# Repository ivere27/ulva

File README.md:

# Ulva

An open-source ESP32-C5 controller board for robotics and controlled-environment agriculture (CEA).

The repository contains a 100 × 100 mm, two-layer carrier PCB, eight KiCad
schematic sheets, project libraries and an ESP-IDF button-input example.
The current board revision is **v0.42**.

- Two CAN FD interfaces with fused 24 V control-power outputs.
- 24 V DC input and an onboard 5 V supply.
- Two I²C buses, peripheral connections and
  [OpenSprinkler-compatible AC/DC expansion](docs/hardware.md#opensprinkler-acdc-expansion).
- OLED, RTC, DHT20, 433 MHz receiver and passive piezo connections.
- Three ADC buttons, a two-switch configuration input and voltage monitoring.

This is a prototype. Full controller firmware and physical validation remain
unfinished. See the [hardware reference](docs/hardware.md) for pin assignments,
power limits and wiring.

## Board views

CAD renders of the current board:

| Front | Back |
| --- | --- |
|  |  |
| **Routing** | **3D assembly** |
|  |  |

[Interactive board viewer](https://ivere27.github.io/ulva/)
· [HTML source](docs/index.html)

Switch between the Routing, 3D, Schematic and Orders tabs. Routing lets you select
traces, vias or pads to highlight a net, search components, switch copper layers,
zoom and save a selection image. Ground pours are omitted; both layers use
front-view coordinates. Schematic provides a thumbnail sidebar for all eight
sheets, with zoom, pan and a PDF download. Orders lets you select JLCPCB assembly
or loose LCSC parts and download supplier files; see the
[order workflow](tools/README.md).

For offline use, keep the complete `docs/` directory and open `docs/index.html`
directly in a browser. In Routing, choose `routing/board.svg` when prompted. In
3D, choose `3d/assembly.json` and `3d/board.glb` together. A local server is optional;
the browser needs explicit file selection to read these data files from disk.
Schematic images, the PDF and Orders open directly without a file picker.

**Version details** shows the board revision, an **Export base** commit and
source/export SHA-256 hashes. Export base records Git HEAD when the metadata was
generated. Each view retains its own recorded source hashes, so older exports
can be distinguished from the current sources.

### 3D assembly

[Open the 3D tab](https://ivere27.github.io/ulva/#3d)
· [Export and usage guide](docs/3d.md)

Rotate, zoom and pan the assembly, or show and hide individual components and
modules. Visibility controls affect the view only. Some component shapes and
module mounting heights are illustrative; the KiCad board remains authoritative.

## Open the project

Open [`ulva_controller.kicad_pro`](ulva_controller.kicad_pro) in KiCad 9 with
its standard symbol and footprint libraries installed. The included project
libraries use relative paths.

| Path | Contents |
| --- | --- |
| `ulva_*.kicad_*` | Schematics, PCB, project settings and design rules |
| `Ulva.kicad_sym`, `Ulva.pretty/` | Project symbols and footprints |
| `Ulva.3dshapes/` | Original terminal-block visualization models |
| [docs/hardware.md](docs/hardware.md) | Hardware and pinout reference |
| [docs/bom.md](docs/bom.md) | Parts and assembly ownership |
| [docs/3d.md](docs/3d.md) | 3D viewer, export and model limitations |
| [tools/](tools/README.md) | JLCPCB and LCSC order preparation and unit tests |
| [scripts/](#verification) | KiCad DRC/ERC validation, SPICE simulation and export runner |
| [firmware/buttons_adc/](firmware/buttons_adc/README.md) | Button example, host unit tests, build and integration instructions |
| `artwork/ulva-icon.svg` | Board icon |

## Verification

Use Python 3.10 or later. Button tests need CMake and a C compiler. CAD checks
use KiCad 9's `kicad-cli` and `pcbnew` module in the same Python environment,
plus `ngspice` for analog checks. Without native KiCad, the runner uses Docker
with the pinned `kicad/kicad:9.0.9` image.

From the repository root, install the rendering dependencies needed for PCB,
Gerber and board-documentation checks, then run the relevant checks:

```sh
python3 -m pip install --target build/preview-python \
  gerbonara==1.5.0 resvg-py==0.2.6
python3 -m unittest discover -s tools
python3 scripts/run_checks.py buttons
python3 scripts/run_checks.py schematic
python3 scripts/run_checks.py pcb
```

The runner checks a disposable snapshot and writes logs and receipts under
ignored `build/runs/`. Use the runner rather than invoking its export helpers
directly. Automated checks do not replace physical hardware validation.

When board images or the routing viewer need regeneration:

```sh
python3 scripts/run_checks.py board-docs
# After reviewing the generated assets, update the images and routing viewer:
python3 scripts/run_checks.py board-docs --update-docs
```

To regenerate the schematic pages and PDF, use Python 3.10 or later and KiCad 9's
`kicad-cli`. Review the output in `build/schematic-docs/`, then publish it:

```sh
python3 scripts/export_schematic_docs.py
python3 scripts/export_schematic_docs.py --update-docs
```

After updating public viewer assets, refresh their version metadata. This reads
the existing files; regenerate any affected view first:

```sh
python3 scripts/export_viewer_info.py
```

## License

Original Ulva design files, firmware, documentation and artwork are released
under the [MIT License](LICENSE). Upstream library data and dependencies retain
their own licenses; see [third-party notices](NOTICE.md).

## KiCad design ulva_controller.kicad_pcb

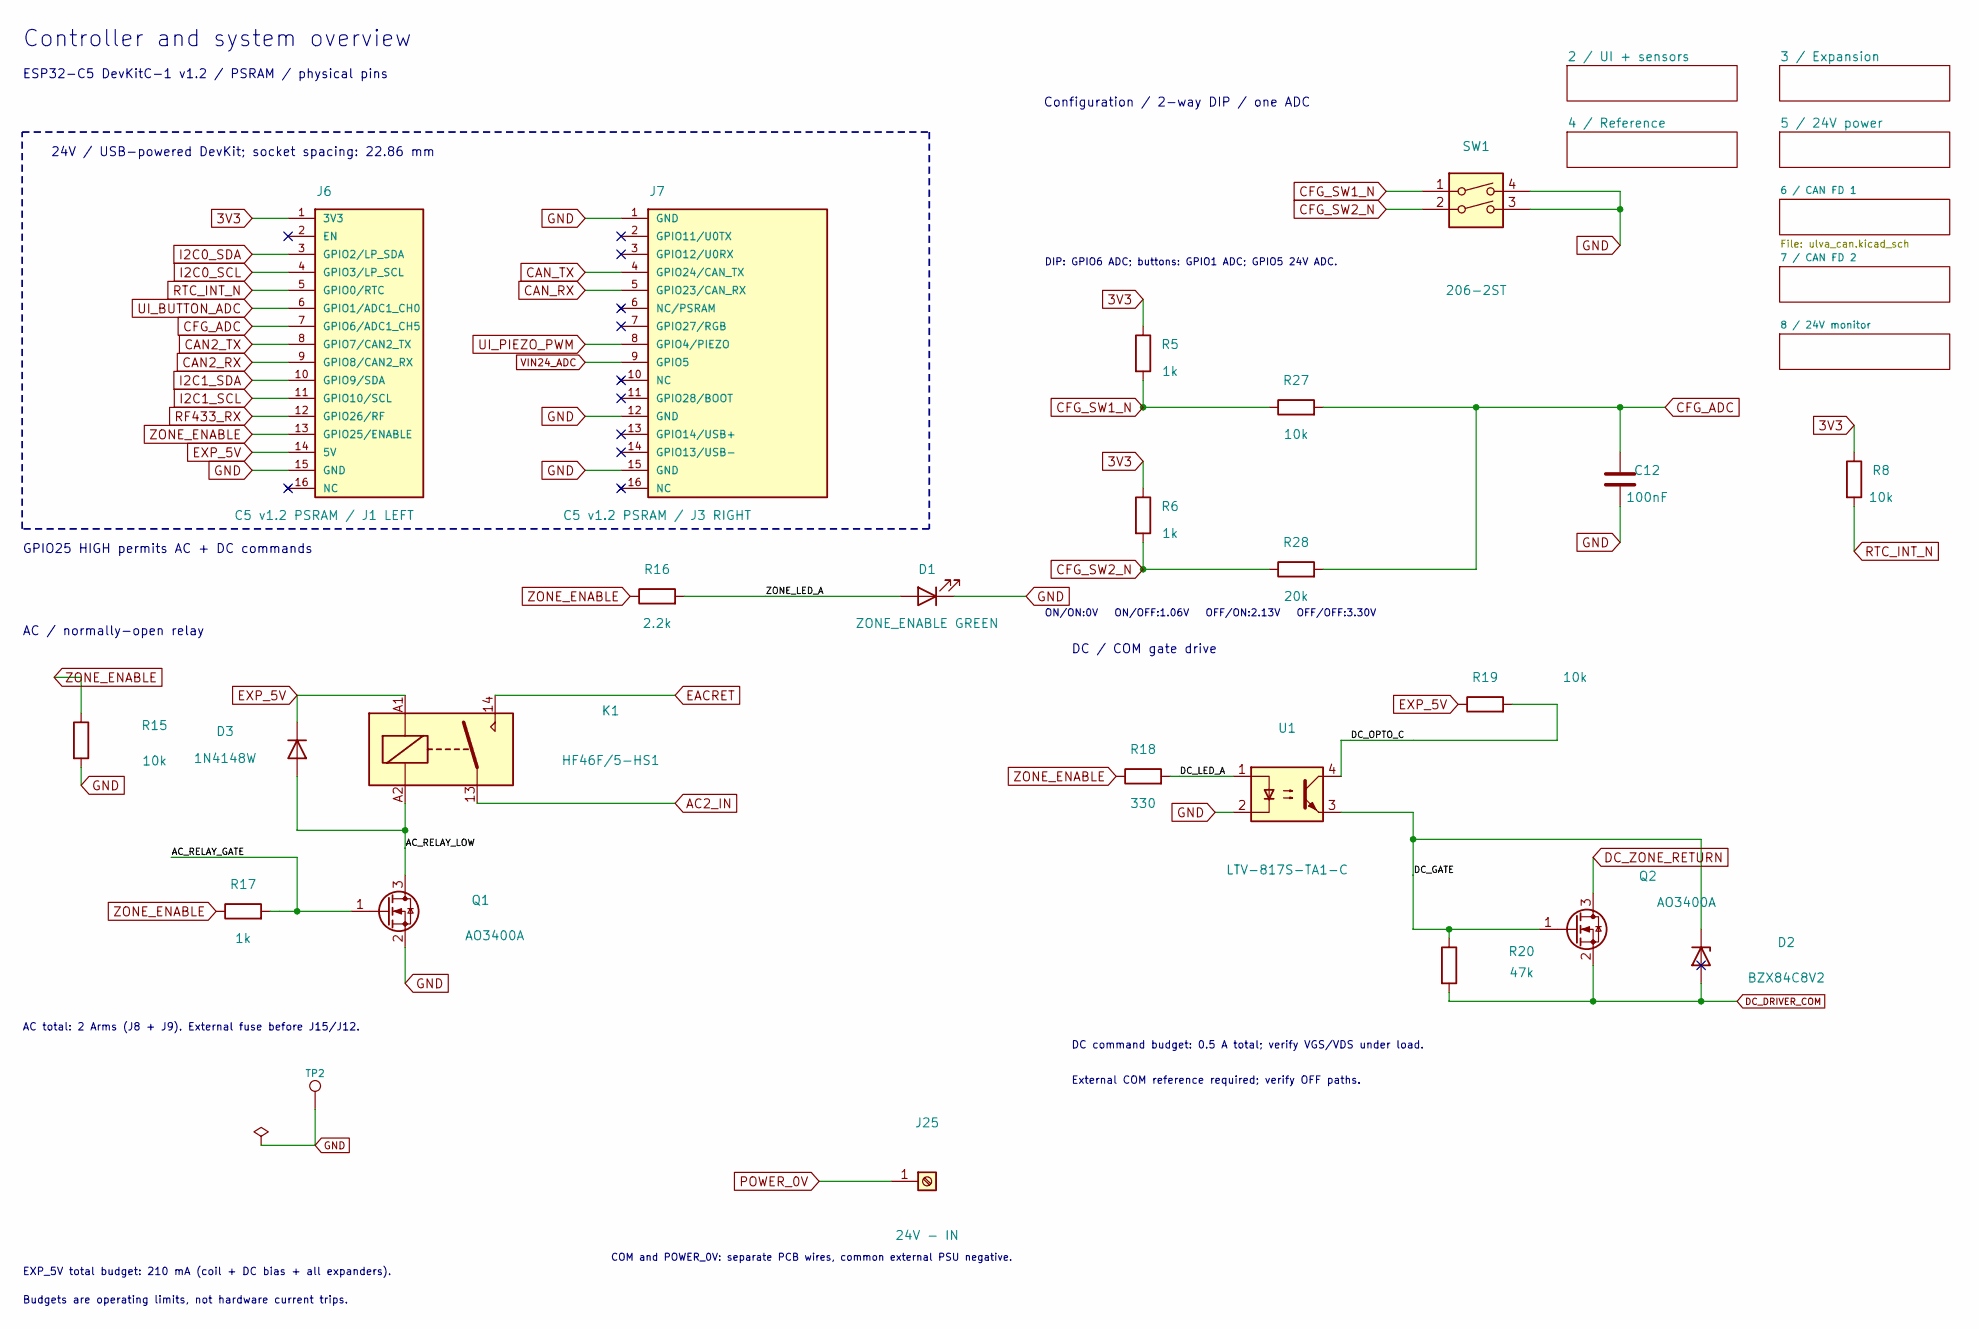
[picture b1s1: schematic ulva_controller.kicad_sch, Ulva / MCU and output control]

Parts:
C12: 100nF; C_0603_1608Metric; MPN CC0603KRX7R9BB104; LCSC C14663
D1: ZONE_ENABLE GREEN; LED_0805_2012Metric; MPN KT-0805G; LCSC C2297
D2: BZX84C8V2; SOT-23; MPN BZX84C8V2; LCSC C22395522
D3: 1N4148W; D_SOD-123; MPN 1N4148W; LCSC C81598
J6: C5 v1.2 PSRAM / J1 LEFT; Samtec_SSW-116-01-G-S_1x16_P2.54mm; MPN SSW-116-01-G-S
J7: C5 v1.2 PSRAM / J3 RIGHT; Samtec_SSW-116-01-G-S_1x16_P2.54mm; MPN SSW-116-01-G-S
J25: 24V - IN; TerminalBlock_MetzConnect_360272_1x01_Horizontal_ScrewM2.6; MPN 360272
K1: HF46F/5-HS1; Relay_SPST_Hongfa_HF46F_HS1; MPN HF46F/5-HS1
Q1, Q2: AO3400A; SOT-23; MPN AO3400A; LCSC C20917
R5, R6, R17: 1k; R_0603_1608Metric; MPN 0603WAF1001T5E; LCSC C21190
R8, R15, R19, R27: 10k; R_0603_1608Metric; MPN 0603WAF1002T5E; LCSC C25804
R16: 2.2k; R_0603_1608Metric; MPN 0603WAF2201T5E; LCSC C4190
R18: 330; R_0603_1608Metric; MPN 0603WAF3300T5E; LCSC C23138
R20: 47k; R_0603_1608Metric; MPN 0603WAF4702T5E; LCSC C25819
R28: 20k; R_0603_1608Metric; MPN 0603WAF2002T5E; LCSC C4184
SW1: 206-2ST; SW_DIP_SPSTx02_Slide_9.78x7.26mm_W7.62mm_P2.54mm; MPN 206-2ST
TP2: GND; TestPoint_Pad_D1.5mm
U1: LTV-817S-TA1-C; SMDIP-4_W9.53mm; MPN LTV-817S-TA1-C; LCSC C109227

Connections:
3V3: J6.1 (3V3), R5.1, R6.1, R8.1; also elsewhere on the board
/AC_RELAY_GATE: Q1.1 (G), R17.2
/AC_RELAY_LOW: D3.2 (A), K1.A2, Q1.3 (D)
/DC_GATE: D2.3 (K), Q2.1 (G), R20.1, U1.3
/DC_LED_A: R18.2, U1.1
/DC_OPTO_C: R19.2, U1.4
/ZONE_LED_A: D1.2 (A), R16.2
AC2_IN: K1.13; also elsewhere on the board
CAN2_RX: J6.9 (GPIO8/CAN2_RX); also elsewhere on the board
CAN2_TX: J6.8 (GPIO7/CAN2_TX); also elsewhere on the board
CAN_RX: J7.5 (GPIO23/CAN_RX); also elsewhere on the board
CAN_TX: J7.4 (GPIO24/CAN_TX); also elsewhere on the board
CFG_ADC: C12.1, J6.7 (GPIO6/ADC1_CH5), R27.2, R28.2
CFG_SW1_N: R5.2, R27.1, SW1.1
CFG_SW2_N: R6.2, R28.1, SW1.2
DC_DRIVER_COM: D2.1 (A), Q2.2 (S), R20.2; also elsewhere on the board
DC_ZONE_RETURN: Q2.3 (D); also elsewhere on the board
EACRET: K1.14; also elsewhere on the board
EXP_5V: D3.1 (K), J6.14 (5V), K1.A1, R19.1; also elsewhere on the board
GND: C12.2, D1.1 (K), J6.15 (GND), J7.1 (GND), J7.12 (GND), J7.15 (GND), Q1.2 (S), R15.2, SW1.3, SW1.4, TP2.1, U1.2; also elsewhere on the board
I2C0_SCL: J6.4 (GPIO3/LP_SCL); also elsewhere on the board
I2C0_SDA: J6.3 (GPIO2/LP_SDA); also elsewhere on the board
I2C1_SCL: J6.11 (GPIO10/SCL); also elsewhere on the board
I2C1_SDA: J6.10 (GPIO9/SDA); also elsewhere on the board
POWER_0V: J25.1; also elsewhere on the board
RF433_RX: J6.12 (GPIO26/RF); also elsewhere on the board
RTC_INT_N: J6.5 (GPIO0/RTC), R8.2; also elsewhere on the board
UI_BUTTON_ADC: J6.6 (GPIO1/ADC1_CH0); also elsewhere on the board
UI_PIEZO_PWM: J7.8 (GPIO4/PIEZO); also elsewhere on the board
VIN24_ADC: J7.9 (GPIO5); also elsewhere on the board
ZONE_ENABLE: J6.13 (GPIO25/ENABLE), R15.1, R16.1, R17.1, R18.1

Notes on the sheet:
Controller and system overview
ESP32-C5 DevKitC-1 v1.2 / PSRAM / physical pins
Configuration / 2-way DIP / one ADC
GPIO25 HIGH permits AC + DC commands
24V / USB-powered DevKit; socket spacing: 22.86 mm
AC / normally-open relay
DC / COM gate drive
AC total: 2 Arms (J8 + J9). External fuse before J15/J12.
DC command budget: 0.5 A total; verify VGS/VDS under load.
EXP_5V total budget: 210 mA (coil + DC bias + all expanders).
Budgets are operating limits, not hardware current trips.
External COM reference required; verify OFF paths.
COM and POWER_0V: separate PCB wires, common external PSU negative.
DIP: GPIO6 ADC; buttons: GPIO1 ADC; GPIO5 24V ADC.
ON/ON:0V ON/OFF:1.06V OFF/ON:2.13V OFF/OFF:3.30V

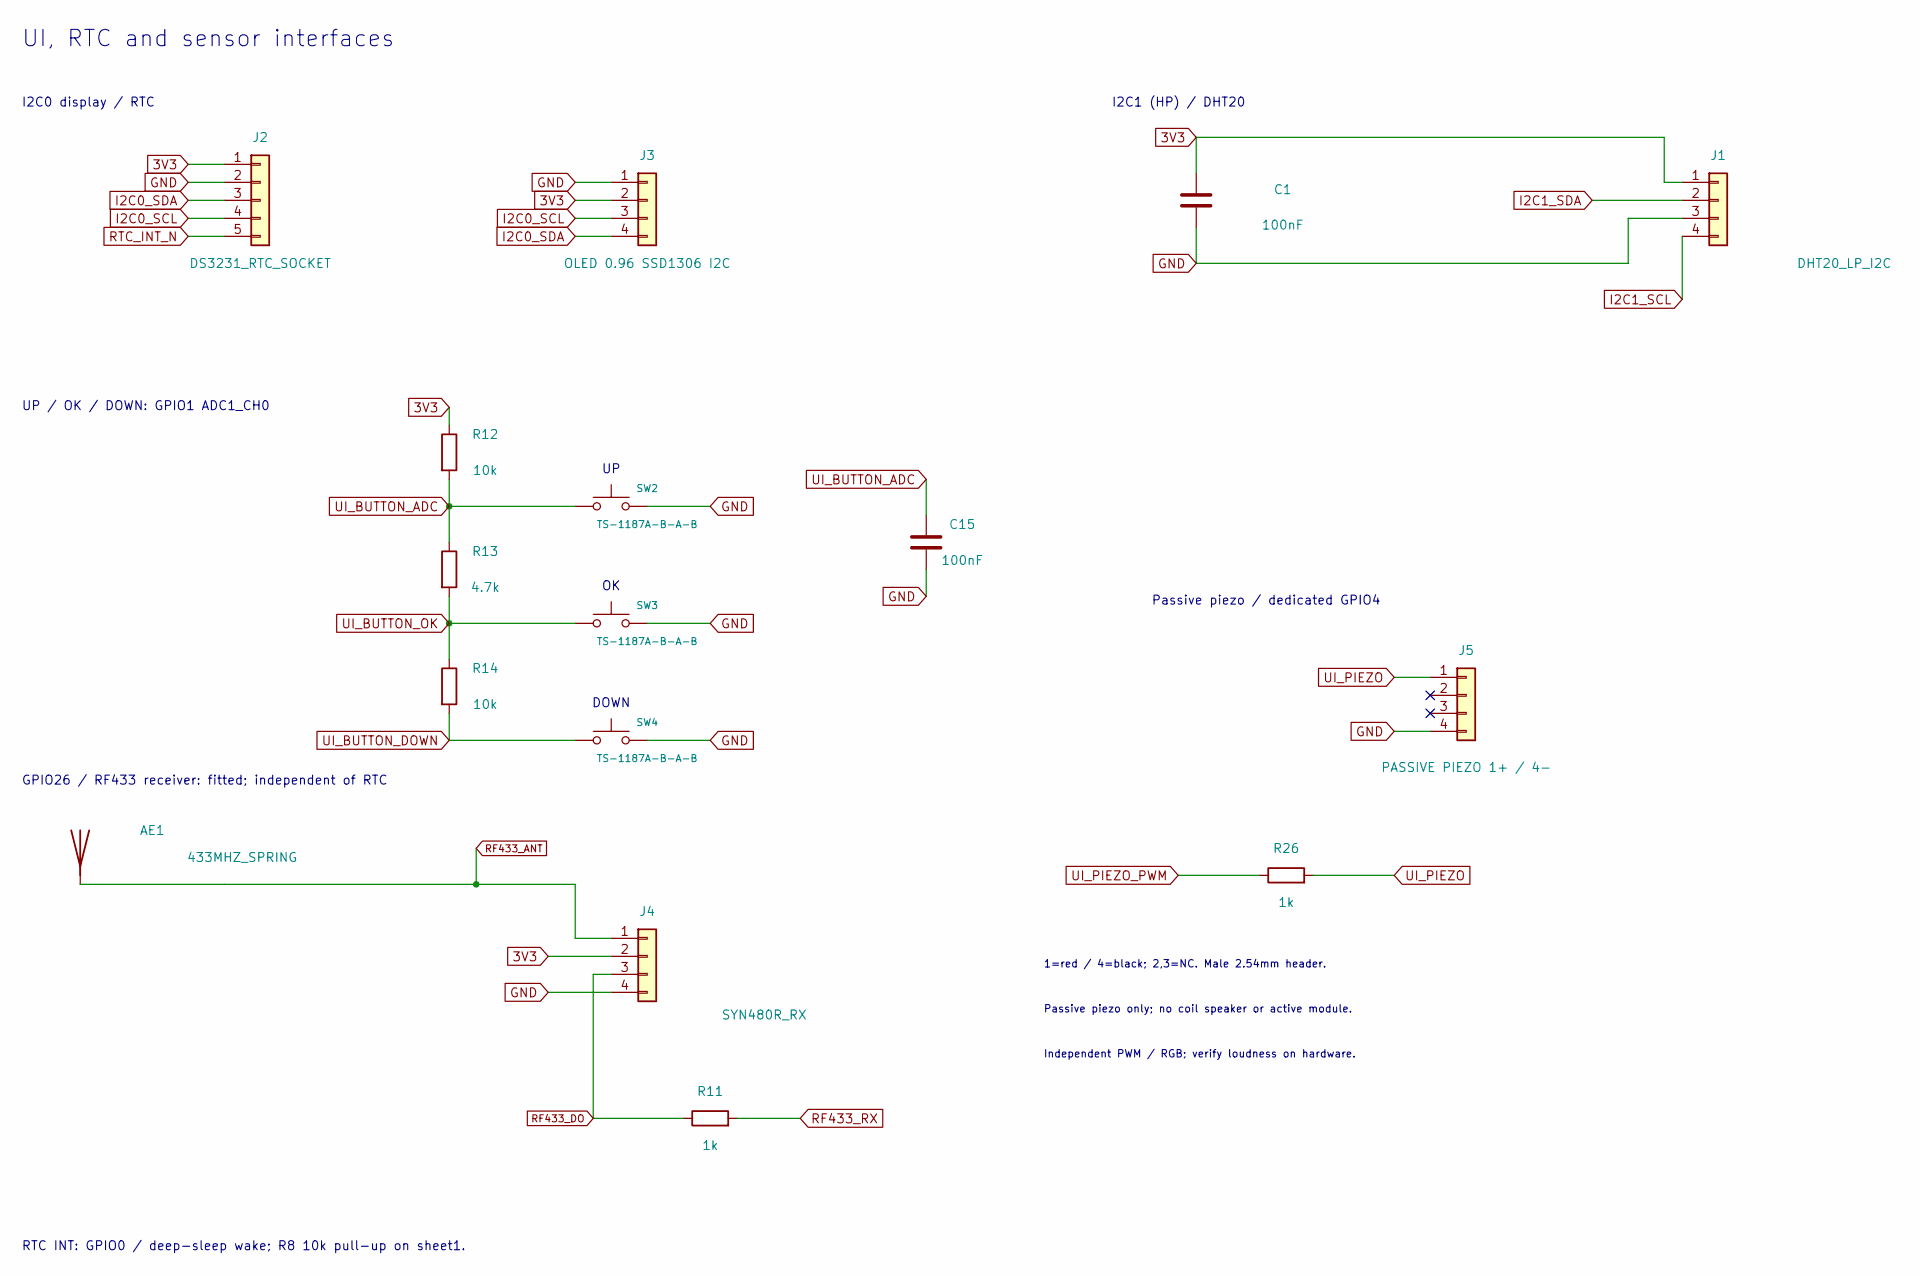
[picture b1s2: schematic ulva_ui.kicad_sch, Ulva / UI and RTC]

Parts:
AE1: 433MHZ_SPRING; TestPoint_THTPad_D2.0mm_Drill1.0mm
C1, C15: 100nF; C_0603_1608Metric; MPN CC0603KRX7R9BB104; LCSC C14663
J1: DHT20_LP_I2C; Samtec_SSW-104-01-G-S_1x04_P2.54mm; MPN SSW-104-01-G-S
J2: DS3231_RTC_SOCKET; Samtec_SSW-105-01-G-S_1x05_P2.54mm; MPN SSW-105-01-G-S
J3: OLED 0.96 SSD1306 I2C; Samtec_SSW-104-01-G-S_1x04_P2.54mm; MPN SSW-104-01-G-S
J4: SYN480R_RX; Samtec_SSW-104-01-G-S_1x04_P2.54mm; MPN SSW-104-01-G-S
J5: PASSIVE PIEZO 1+ / 4-; PinHeader_1x04_P2.54mm_Vertical
R11, R26: 1k; R_0603_1608Metric; MPN 0603WAF1001T5E; LCSC C21190
R12, R14: 10k; R_0603_1608Metric; MPN 0603WAF1002T5E; LCSC C25804
R13: 4.7k; R_0603_1608Metric; MPN 0603WAF4701T5E; LCSC C23162
SW2, SW3, SW4: TS-1187A-B-A-B; SW_XKB_TS-1187A_5.1x5.1mm; MPN TS-1187A-B-A-B; LCSC C318884

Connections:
3V3: C1.1, J1.1, J2.1, J3.2, J4.2, R12.1; also elsewhere on the board
GND: C1.2, C15.2, J1.3, J2.2, J3.1, J4.4, J5.4, SW2.2, SW3.2, SW4.2; also elsewhere on the board
I2C0_SCL: J2.4, J3.3; also elsewhere on the board
I2C0_SDA: J2.3, J3.4; also elsewhere on the board
I2C1_SCL: J1.4; also elsewhere on the board
I2C1_SDA: J1.2; also elsewhere on the board
RF433_ANT: AE1.1 (A), J4.1
RF433_DO: J4.3, R11.1
RF433_RX: R11.2; also elsewhere on the board
RTC_INT_N: J2.5; also elsewhere on the board
UI_BUTTON_ADC: C15.1, R12.2, R13.1, SW2.1; also elsewhere on the board
UI_BUTTON_DOWN: R14.2, SW4.1
UI_BUTTON_OK: R13.2, R14.1, SW3.1
UI_PIEZO: J5.1, R26.2
UI_PIEZO_PWM: R26.1; also elsewhere on the board

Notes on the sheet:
UI, RTC and sensor interfaces
I2C0 display / RTC
I2C1 (HP) / DHT20
UP / OK / DOWN: GPIO1 ADC1_CH0
GPIO26 / RF433 receiver: fitted; independent of RTC
RTC INT: GPIO0 / deep-sleep wake; R8 10k pull-up on sheet1.
Passive piezo / dedicated GPIO4
1=red / 4=black; 2,3=NC. Male 2.54mm header.
Passive piezo only; no coil speaker or active module.
Independent PWM / RGB; verify loudness on hardware.
DOWN

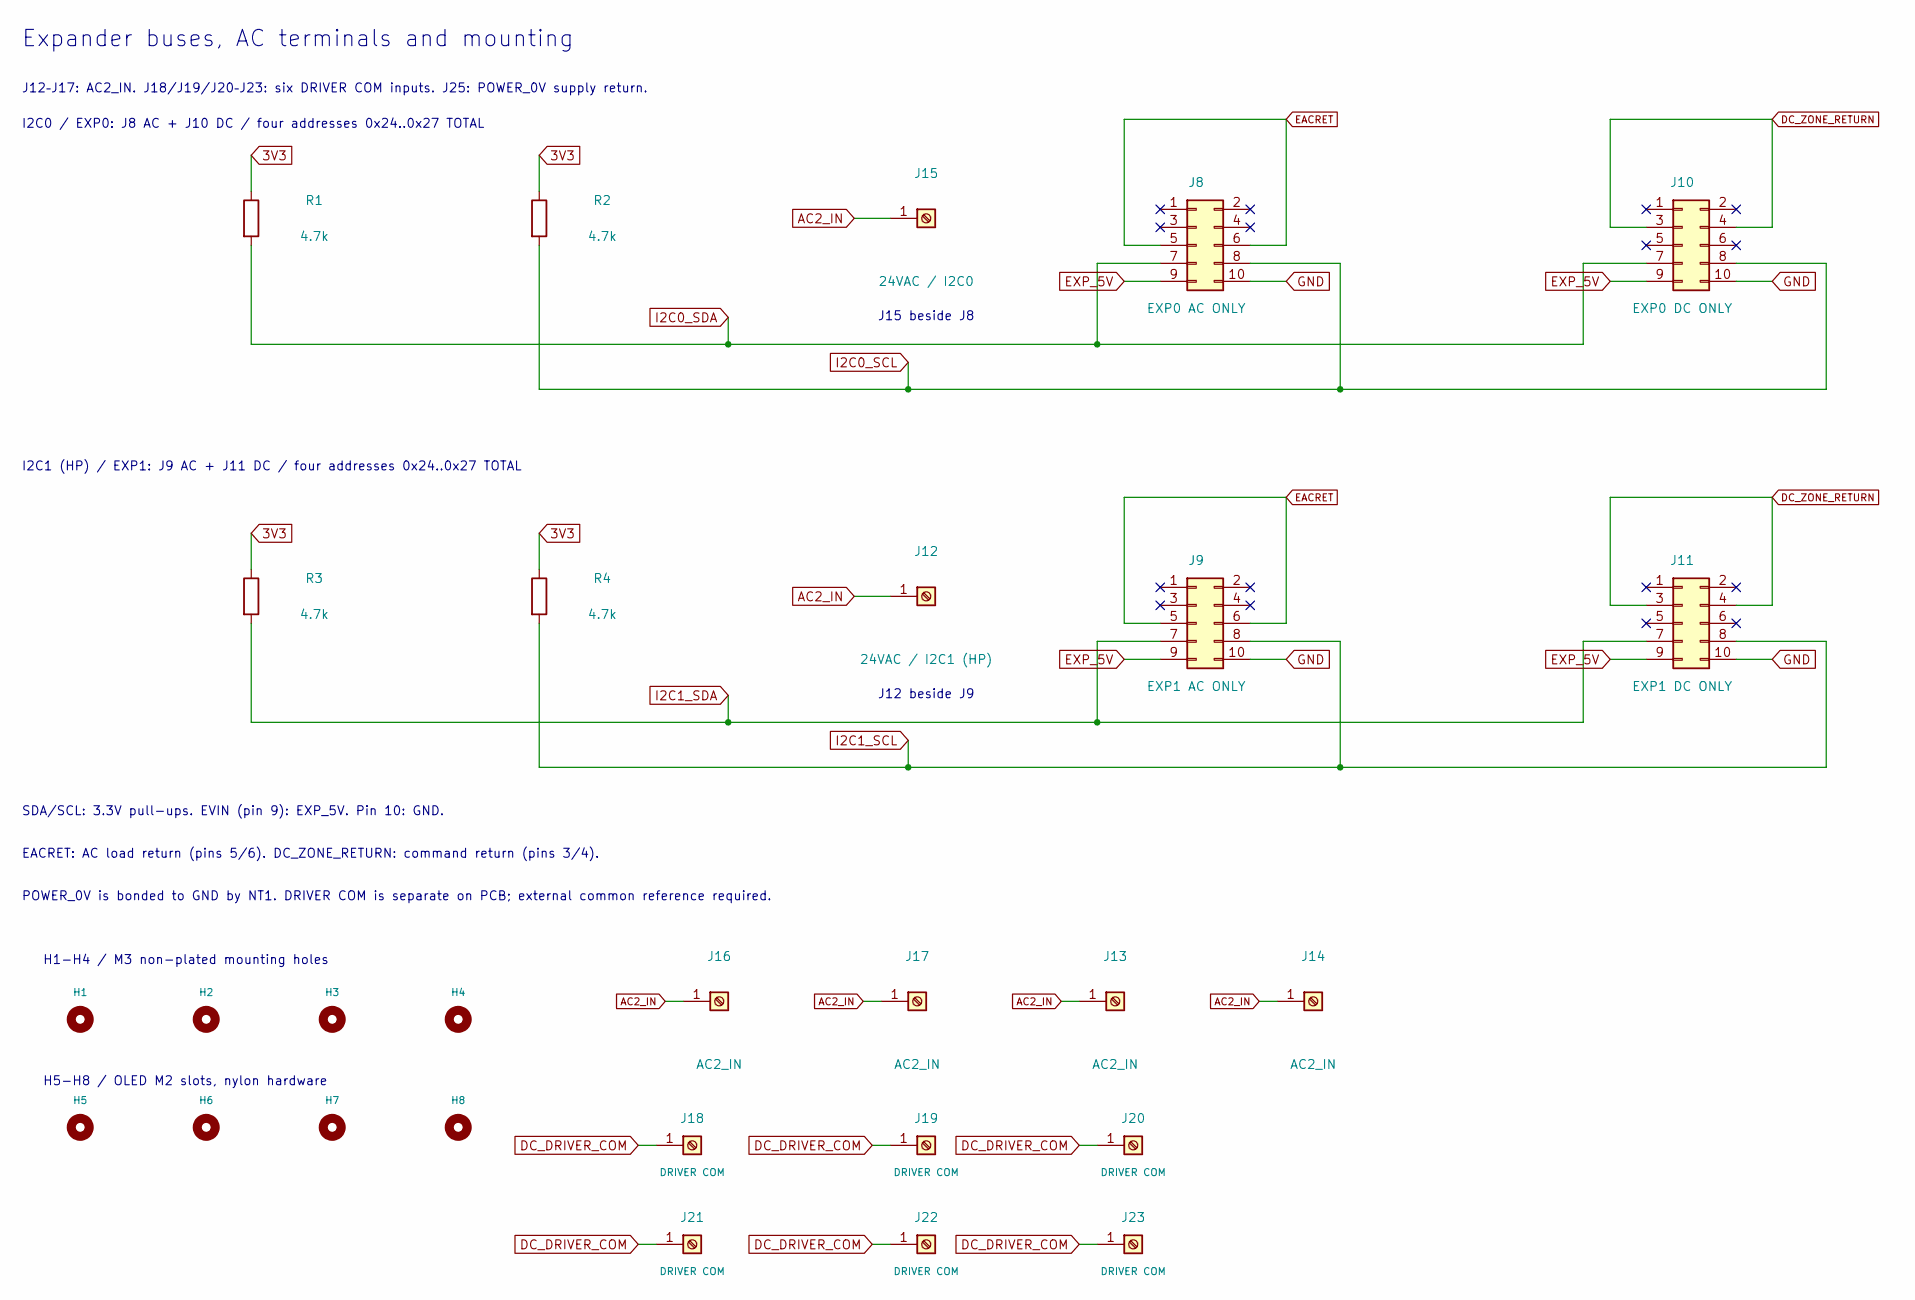
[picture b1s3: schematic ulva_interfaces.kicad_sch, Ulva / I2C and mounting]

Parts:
H1, H2, H3, H4: M3 NPTH; MountingHole_3.2mm_M3
H5, H6, H7, H8: OLED M2 SLOT; MountingSlot_4.0x2.7mm_M2_OLED
J8: EXP0 AC ONLY; ZHOURI_DC3-2.54-10PAS_IDC_2x05_P2.54mm; MPN DC3-2.54-10PAS; LCSC C2977596
J9: EXP1 AC ONLY; ZHOURI_DC3-2.54-10PAS_IDC_2x05_P2.54mm; MPN DC3-2.54-10PAS; LCSC C2977596
J10: EXP0 DC ONLY; ZHOURI_DC3-2.54-10PAS_IDC_2x05_P2.54mm; MPN DC3-2.54-10PAS; LCSC C2977596
J11: EXP1 DC ONLY; ZHOURI_DC3-2.54-10PAS_IDC_2x05_P2.54mm; MPN DC3-2.54-10PAS; LCSC C2977596
J12: 24VAC / I2C1 (HP); TerminalBlock_MetzConnect_360272_1x01_Horizontal_ScrewM2.6; MPN 360272
J13, J14, J16, J17: AC2_IN; TerminalBlock_MetzConnect_360272_1x01_Horizontal_ScrewM2.6; MPN 360272
J15: 24VAC / I2C0; TerminalBlock_MetzConnect_360272_1x01_Horizontal_ScrewM2.6; MPN 360272
J18, J19, J20, J21, J22, J23: DRIVER COM; TerminalBlock_MetzConnect_360272_1x01_Horizontal_ScrewM2.6; MPN 360272
R1, R2, R3, R4: 4.7k; R_0603_1608Metric; MPN 0603WAF4701T5E; LCSC C23162

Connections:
3V3: R1.1, R2.1, R3.1, R4.1; also elsewhere on the board
AC2_IN: J12.1, J13.1, J14.1, J15.1, J16.1, J17.1; also elsewhere on the board
DC_DRIVER_COM: J18.1, J19.1, J20.1, J21.1, J22.1, J23.1; also elsewhere on the board
DC_ZONE_RETURN: J10.3, J10.4, J11.3, J11.4; also elsewhere on the board
EACRET: J8.5, J8.6, J9.5, J9.6; also elsewhere on the board
EXP_5V: J8.9, J9.9, J10.9, J11.9; also elsewhere on the board
GND: J8.10, J9.10, J10.10, J11.10; also elsewhere on the board
I2C0_SCL: J8.8, J10.8, R2.2; also elsewhere on the board
I2C0_SDA: J8.7, J10.7, R1.2; also elsewhere on the board
I2C1_SCL: J9.8, J11.8, R4.2; also elsewhere on the board
I2C1_SDA: J9.7, J11.7, R3.2; also elsewhere on the board

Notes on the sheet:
Expander buses, AC terminals and mounting
I2C0 / EXP0: J8 AC + J10 DC / four addresses 0x24..0x27 TOTAL
I2C1 (HP) / EXP1: J9 AC + J11 DC / four addresses 0x24..0x27 TOTAL
SDA/SCL: 3.3V pull-ups. EVIN (pin 9): EXP_5V. Pin 10: GND.
EACRET: AC load return (pins 5/6). DC_ZONE_RETURN: command return (pins 3/4).
POWER_0V is bonded to GND by NT1. DRIVER COM is separate on PCB; external common reference required.
H1-H4 / M3 non-plated mounting holes
H5-H8 / OLED M2 slots, nylon hardware
J15 beside J8
J12 beside J9
J12–J17: AC2_IN. J18/J19/J20–J23: six DRIVER COM inputs. J25: POWER_0V supply return.

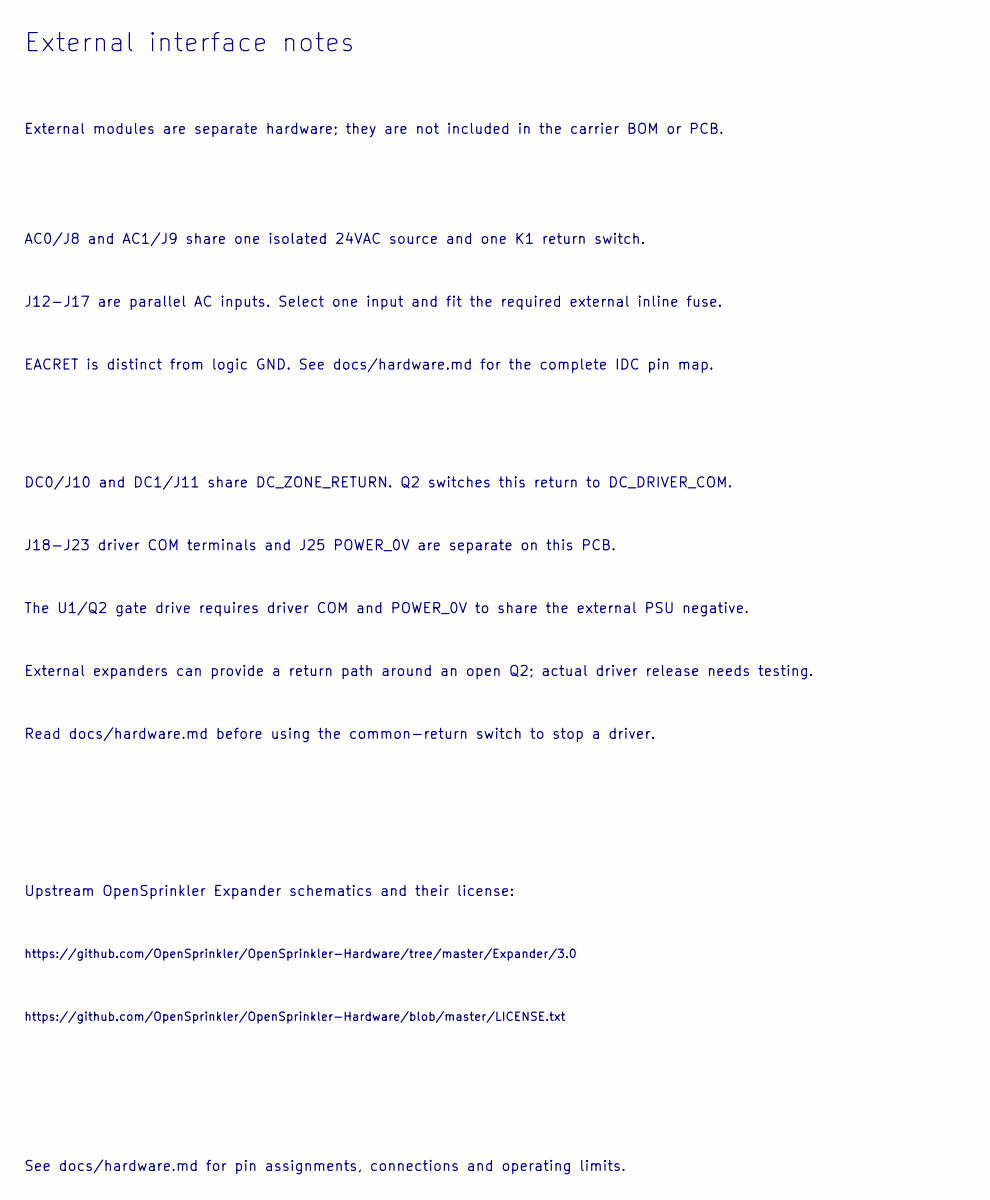
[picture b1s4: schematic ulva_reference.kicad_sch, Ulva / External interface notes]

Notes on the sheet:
External interface notes
External modules are separate hardware; they are not included in the carrier BOM or PCB.
AC0/J8 and AC1/J9 share one isolated 24VAC source and one K1 return switch.
J12-J17 are parallel AC inputs. Select one input and fit the required external inline fuse.
EACRET is distinct from logic GND. See docs/hardware.md for the complete IDC pin map.
DC0/J10 and DC1/J11 share DC_ZONE_RETURN. Q2 switches this return to DC_DRIVER_COM.
J18-J23 driver COM terminals and J25 POWER_0V are separate on this PCB.
The U1/Q2 gate drive requires driver COM and POWER_0V to share the external PSU negative.
External expanders can provide a return path around an open Q2; actual driver release needs testing.
Read docs/hardware.md before using the common-return switch to stop a driver.
Upstream OpenSprinkler Expander schematics and their license:
https://github.com/OpenSprinkler/OpenSprinkler-Hardware/tree/master/Expander/3.0
https://github.com/OpenSprinkler/OpenSprinkler-Hardware/blob/master/LICENSE.txt
See docs/hardware.md for pin assignments, connections and operating limits.

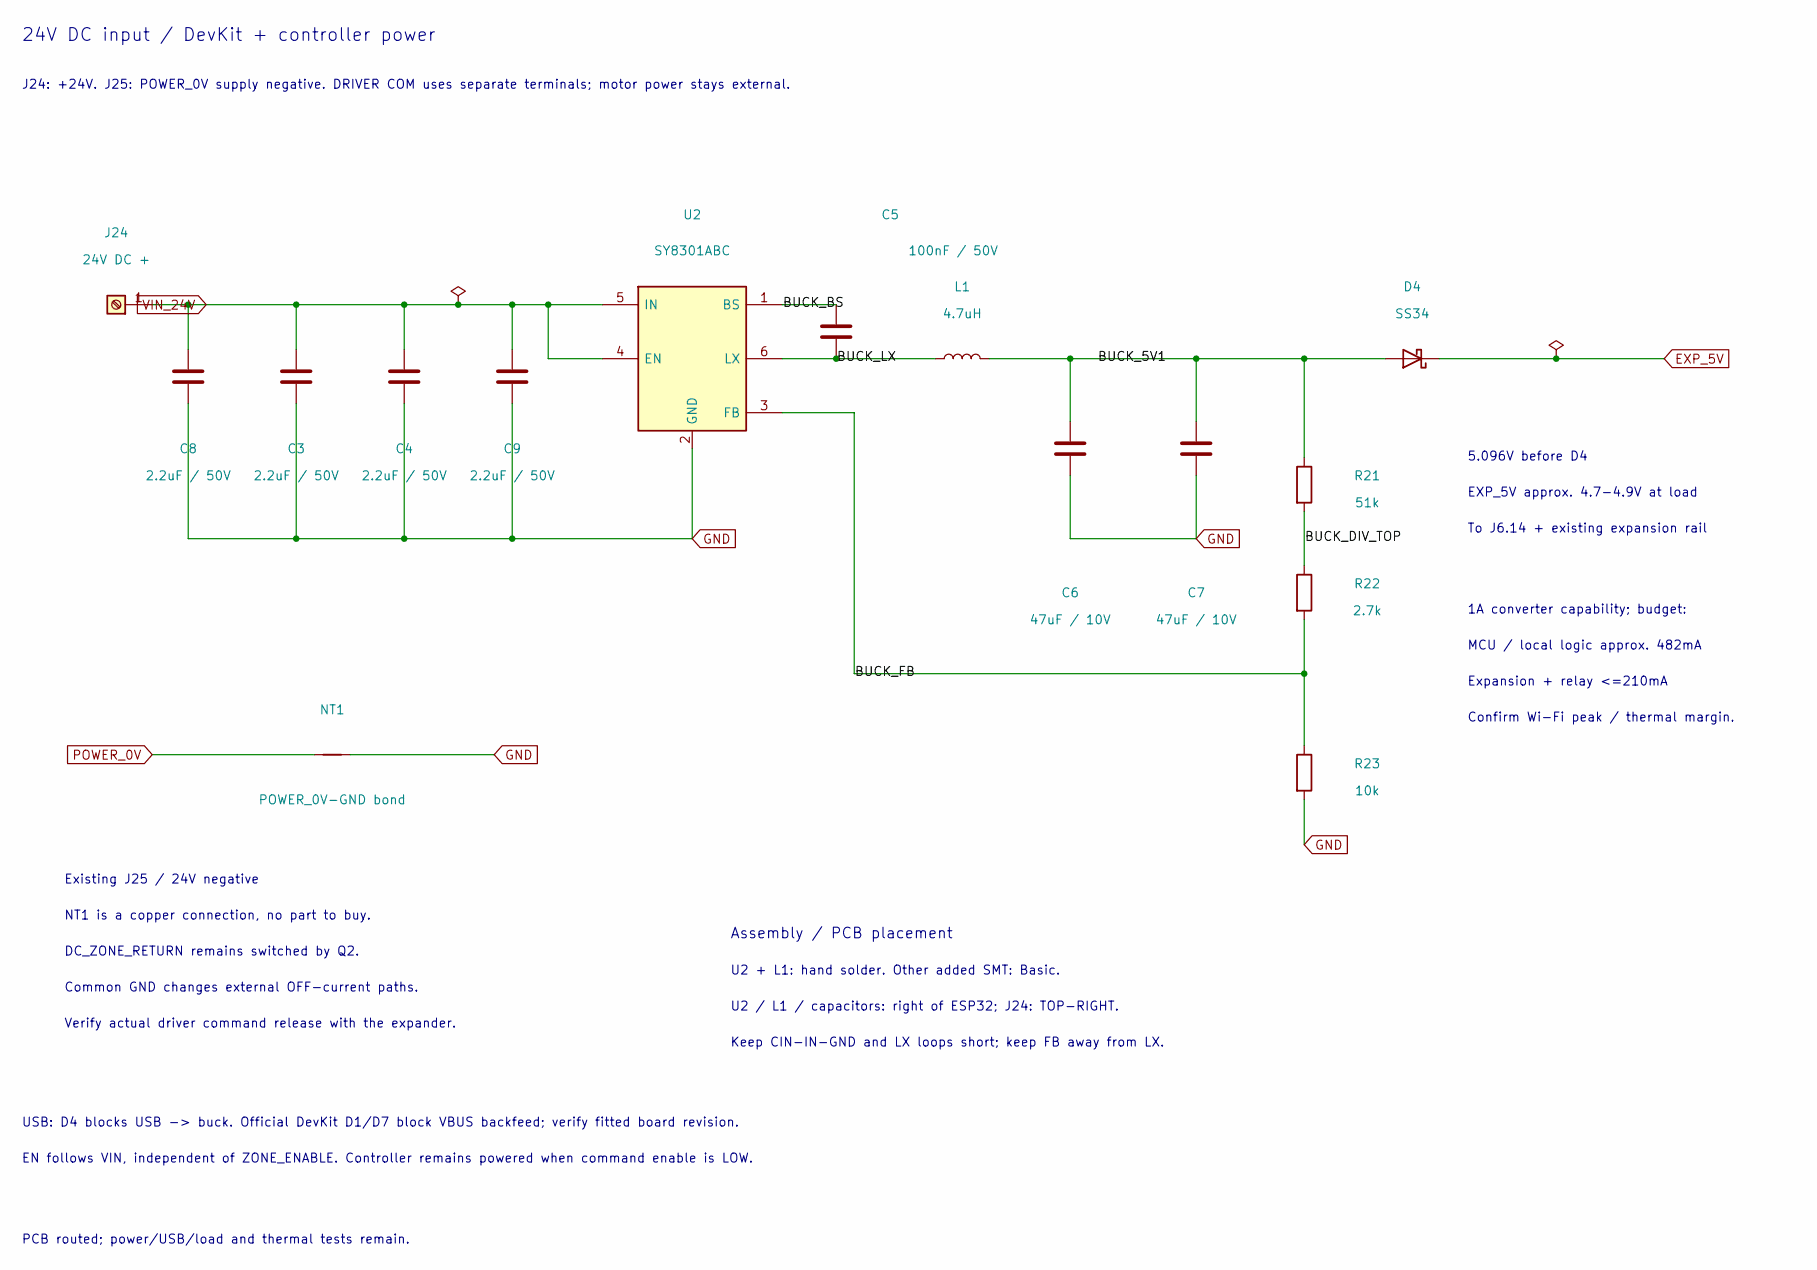
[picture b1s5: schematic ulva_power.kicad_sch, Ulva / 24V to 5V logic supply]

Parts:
C3, C4, C8, C9: 2.2uF / 50V; C_1206_3216Metric; MPN CL31B225KBHNNNE; LCSC C50254
C5: 100nF / 50V; C_0603_1608Metric; MPN CC0603KRX7R9BB104; LCSC C14663
C6, C7: 47uF / 10V; C_1206_3216Metric; MPN CL31A476MPHNNNE; LCSC C96123
D4: SS34; D_SMA; MPN SS34; LCSC C8678
J24: 24V DC +; TerminalBlock_MetzConnect_360272_1x01_Horizontal_ScrewM2.6; MPN 360272
L1: 4.7uH; L_Sunlord_SWPA6045_6x6mm; MPN SWPA6045S4R7MT; LCSC C78804
NT1: POWER_0V-GND bond; NetTie-2_SMD_Pad2.0mm
R21: 51k; R_0603_1608Metric; MPN 0603WAF5102T5E; LCSC C23196
R22: 2.7k; R_0603_1608Metric; MPN 0603WAF2701T5E; LCSC C13167
R23: 10k; R_0603_1608Metric; MPN 0603WAF1002T5E; LCSC C25804
U2: SY8301ABC; SOT-23-6_Handsoldering; MPN SY8301ABC; LCSC C2927130

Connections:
/5 / 24V power/BUCK_5V1: C6.1, C7.1, D4.2 (A), L1.2, R21.1
/5 / 24V power/BUCK_BS: C5.1, U2.1 (BS)
/5 / 24V power/BUCK_DIV_TOP: R21.2, R22.1
/5 / 24V power/BUCK_FB: R22.2, R23.1, U2.3 (FB)
/5 / 24V power/BUCK_LX: C5.2, L1.1, U2.6 (LX)
EXP_5V: D4.1 (K); also elsewhere on the board
GND: C3.2, C4.2, C6.2, C7.2, C8.2, C9.2, NT1.2, R23.2, U2.2 (GND); also elsewhere on the board
POWER_0V: NT1.1; also elsewhere on the board
VIN_24V: C3.1, C4.1, C8.1, C9.1, J24.1, U2.4 (EN), U2.5 (IN); also elsewhere on the board

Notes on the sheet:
24V DC input / DevKit + controller power
J24: +24V. J25: POWER_0V supply negative. DRIVER COM uses separate terminals; motor power stays external.
5.096V before D4
EXP_5V approx. 4.7-4.9V at load
To J6.14 + existing expansion rail
1A converter capability; budget:
MCU / local logic approx. 482mA
Expansion + relay <=210mA
Confirm Wi-Fi peak / thermal margin.
Existing J25 / 24V negative
NT1 is a copper connection, no part to buy.
DC_ZONE_RETURN remains switched by Q2.
Common GND changes external OFF-current paths.
Verify actual driver command release with the expander.
Assembly / PCB placement
U2 + L1: hand solder. Other added SMT: Basic.
U2 / L1 / capacitors: right of ESP32; J24: TOP-RIGHT.
Keep CIN-IN-GND and LX loops short; keep FB away from LX.
USB: D4 blocks USB -> buck. Official DevKit D1/D7 block VBUS backfeed; verify fitted board revision.
EN follows VIN, independent of ZONE_ENABLE. Controller remains powered when command enable is LOW.
PCB routed; power/USB/load and thermal tests remain.

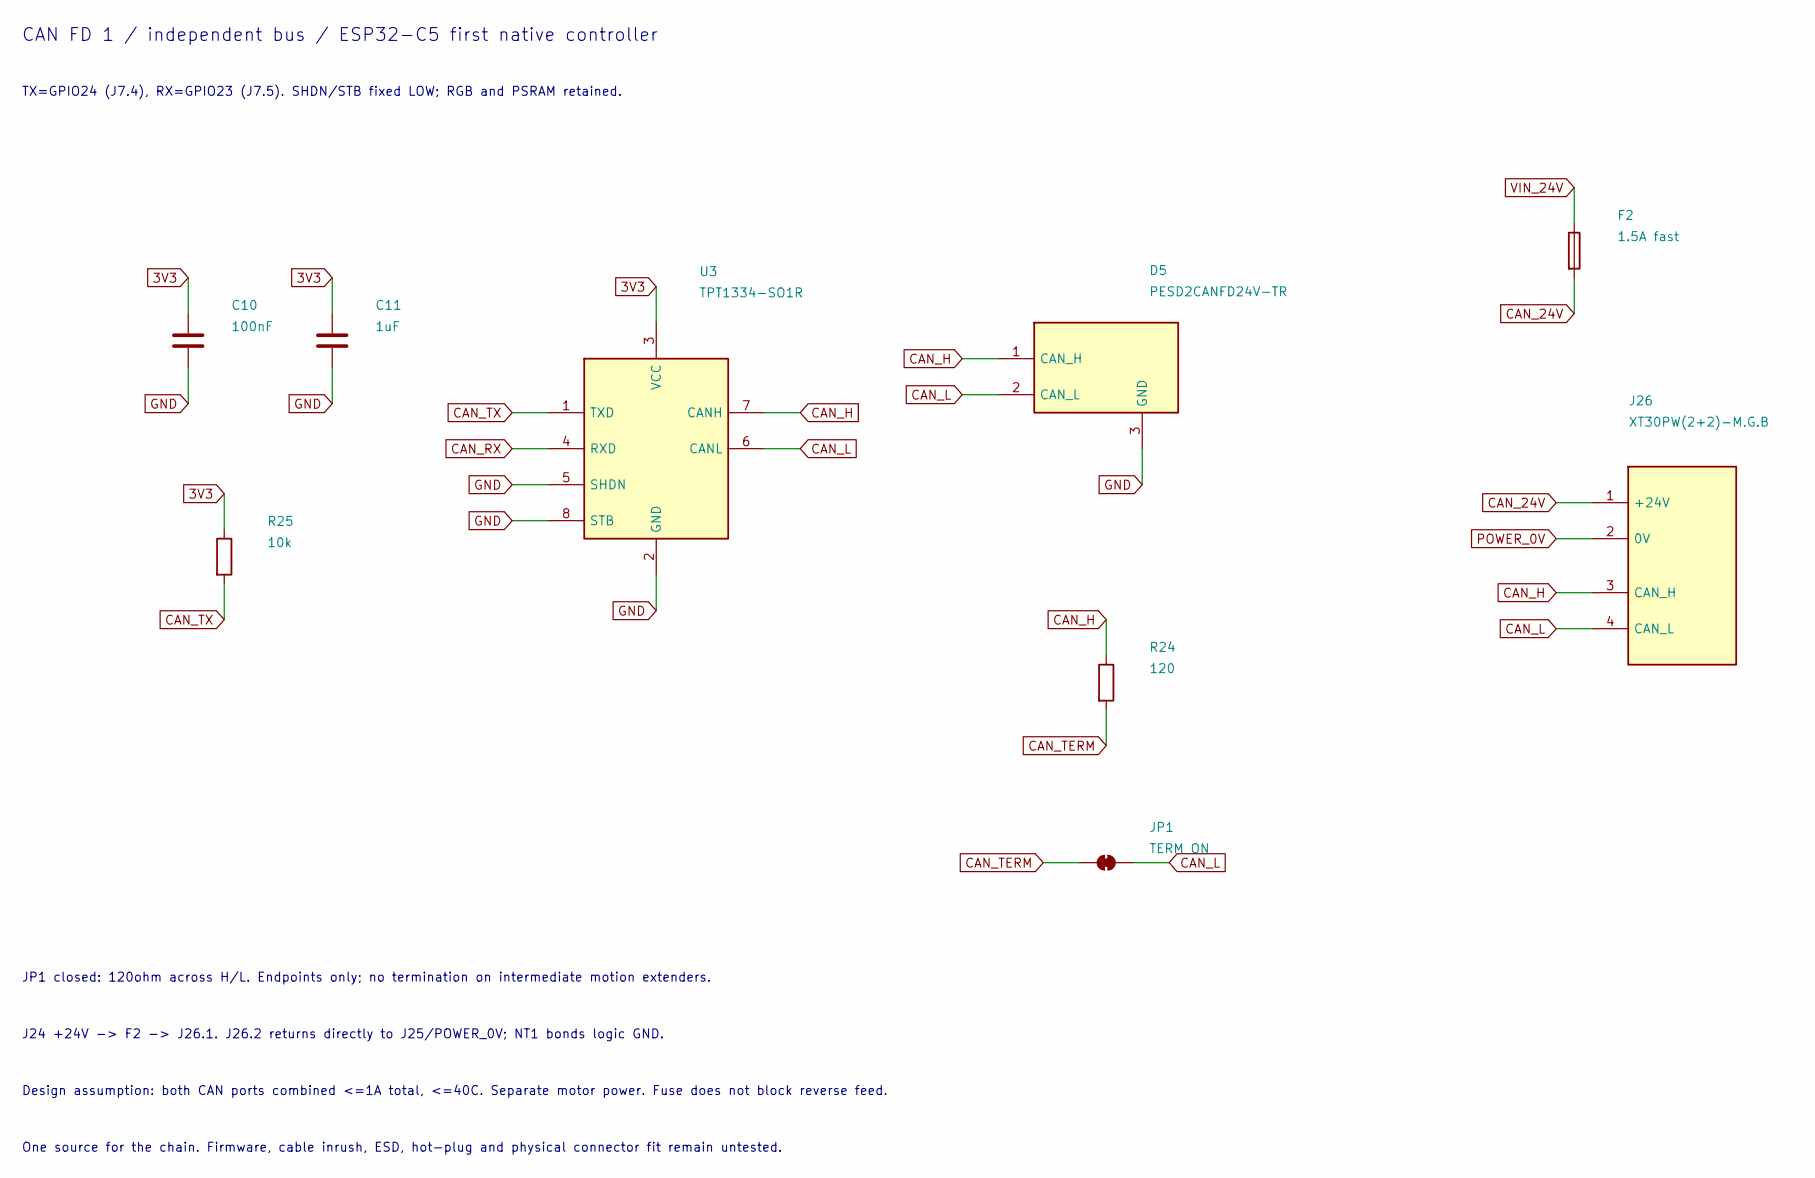
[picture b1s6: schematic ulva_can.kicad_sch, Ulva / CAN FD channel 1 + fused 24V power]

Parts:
C10: 100nF; C_0603_1608Metric; MPN CC0603KRX7R9BB104; LCSC C14663
C11: 1uF; C_0603_1608Metric; MPN CL10A105KB8NNNC; LCSC C15849
D5: PESD2CANFD24V-TR; SOT-23; MPN PESD2CANFD24V-TR; LCSC C552486
F2: 1.5A fast; Fuse_Littelfuse_467_0603; MPN 046701.5NRHF; LCSC C187608
J26: XT30PW(2+2)-M.G.B; AMASS_XT30PW_2plus2_M_Horizontal; MPN XT30PW(2+2)-M.G.B; LCSC C19268030
JP1: TERM ON; SolderJumper-2_P1.3mm_Bridged_Pad1.0x1.5mm
R24: 120; R_1206_3216Metric; MPN 1206W4F1200T5E; LCSC C17909
R25: 10k; R_0603_1608Metric; MPN 0603WAF1002T5E; LCSC C25804
U3: TPT1334-SO1R; SOIC-8_3.9x4.9mm_P1.27mm; MPN TPT1334-SO1R; LCSC C44859616

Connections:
3V3: C10.1, C11.1, R25.1, U3.3 (VCC); also elsewhere on the board
CAN_24V: F2.2, J26.1 (+24V)
CAN_H: D5.1 (CAN_H), J26.3 (CAN_H), R24.1, U3.7 (CANH)
CAN_L: D5.2 (CAN_L), J26.4 (CAN_L), JP1.2 (B), U3.6 (CANL)
CAN_RX: U3.4 (RXD); also elsewhere on the board
CAN_TERM: JP1.1 (A), R24.2
CAN_TX: R25.2, U3.1 (TXD); also elsewhere on the board
GND: C10.2, C11.2, D5.3 (GND), U3.2 (GND), U3.5 (SHDN), U3.8 (STB); also elsewhere on the board
POWER_0V: J26.2 (0V); also elsewhere on the board
VIN_24V: F2.1; also elsewhere on the board

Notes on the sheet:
CAN FD 1 / independent bus / ESP32-C5 first native controller
TX=GPIO24 (J7.4), RX=GPIO23 (J7.5). SHDN/STB fixed LOW; RGB and PSRAM retained.
JP1 closed: 120ohm across H/L. Endpoints only; no termination on intermediate motion extenders.
J24 +24V -> F2 -> J26.1. J26.2 returns directly to J25/POWER_0V; NT1 bonds logic GND.
Design assumption: both CAN ports combined <=1A total, <=40C. Separate motor power. Fuse does not block reverse feed.
One source for the chain. Firmware, cable inrush, ESD, hot-plug and physical connector fit remain untested.
